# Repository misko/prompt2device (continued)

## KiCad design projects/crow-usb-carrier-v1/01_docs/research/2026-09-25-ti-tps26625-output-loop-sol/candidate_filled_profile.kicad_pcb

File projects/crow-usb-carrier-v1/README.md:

# crow-usb-carrier-v1

PCB commissioning scaffold. The original request and acceptance criteria live in [`01_docs/BRIEF.md`](01_docs/BRIEF.md); current work lives in [`01_docs/STATUS.md`](01_docs/STATUS.md).

## Capability

- target: `design`
- signal integrity: `high_speed_digital`
- assembly: `jlcpcb`
- firmware: `forbidden`
- foreign mating: `false`
- enclosure seed: `false`

The machine-readable authority is [`01_docs/capability-profile.json`](01_docs/capability-profile.json).

## Start

Run this from the project root. If this project is outside the circuits checkout, export `CIRCUITS_ROOT=/absolute/path/to/circuits` first.

```bash
export CIRCUITS_ROOT="${CIRCUITS_ROOT:-$(git rev-parse --show-toplevel 2>/dev/null)}"
test -f "$CIRCUITS_ROOT/skills/pcb-design/SKILL.md" || { \
  echo "set CIRCUITS_ROOT to the circuits checkout" >&2; exit 2; }
python3 "$CIRCUITS_ROOT/skills/pcb-design/scripts/skill_reference_router.py" \
  --profile "$PWD/01_docs/capability-profile.json" \
  --at-stage PCB-COMMISSION --json
```

This is a scaffold, not a passed commission. Read [`01_docs/COMMISSIONING-HOLD.md`](01_docs/COMMISSIONING-HOLD.md), preserve the original brief, close its fact locks, and replace or explicitly adopt every seeded example. Do not run either rebuild conductor while the hold exists; both fail closed.

Current source state is a reviewed 569-component / 65-reference ADC proposal,
including the planned `C_ADC_3V3X_OK_VDD` supervisor bypass and a project-only
P-MOD ordering repair. It has no new producer, schematic checkpoint, native
board, P2 acceptance, or release status. Earlier 568-component generated
artifacts remain historical evidence and must not be rebound; see
[`01_docs/STATUS.md`](01_docs/STATUS.md) before any conductor admission.

The current CJ is `1f01be73…` and is conditionally bound only to the reviewed
source E-FAULT clarification; complete fitted-board waveform qualification is
still required. The reviewed 18-pose power source backtrack is planned
placement, not native acceptance.

After the separately typed commission, architecture, and sourcing admission evidence is reviewed and its hold is removed, start the full conductor with `bash 03_src/rebuild_all.sh`. A fresh run deliberately stops at evidence and operator checkpoints. After accepting the exact schematic review checkpoint, continue without rebuilding TSX using `bash 03_src/rebuild_all.sh --resume-after-schematic-review`. A sealed release is immutable and does not by itself mean this board was ordered.

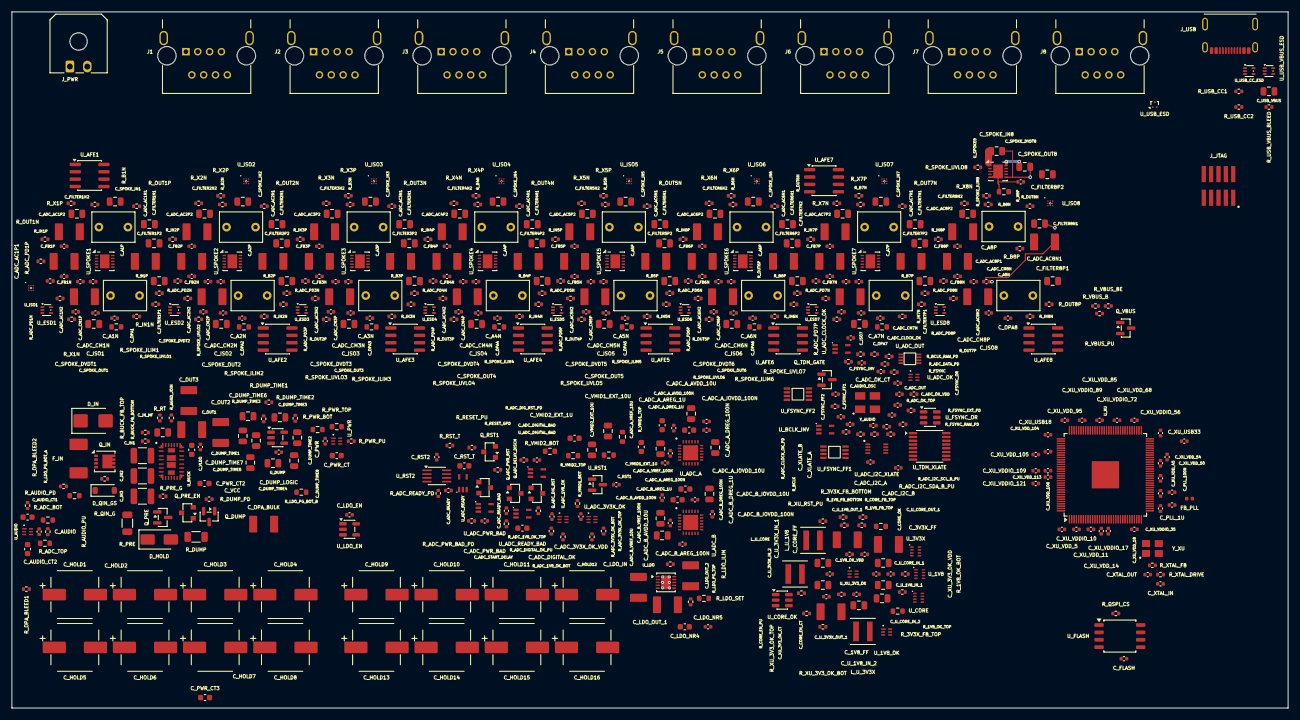
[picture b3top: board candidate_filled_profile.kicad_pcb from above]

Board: 4 copper layers, 220.0 x 120.0 mm, 569 parts (0 on the bottom side), 282 nets.

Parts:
C_1V8_FF, C_3V3X_FF: 120pF; C_0402_1005Metric
C_1V8_OK_VDD: 100nF; C_0402_1005Metric
C_A1N, C_A1P, C_A2N, C_A2P, C_A3N, C_A3P, C_A4N, C_A4P, C_A5N, C_A5P, C_A6N, C_A6P, C_A7N, C_A7P, C_A8N, C_A8P: 1uF; C_Rect_L7.2mm_W5.0mm_P5.00mm
C_ADC_3V3X_OK_VDD: 100nF; C_0402_1005Metric
C_ADC_AC1N1, C_ADC_AC1N2, C_ADC_AC1P1, C_ADC_AC1P2, C_ADC_AC2N1, C_ADC_AC2N2, C_ADC_AC2P1, C_ADC_AC2P2, C_ADC_AC3N1, C_ADC_AC3N2, C_ADC_AC3P1, C_ADC_AC3P2, C_ADC_AC4N1, C_ADC_AC4N2, C_ADC_AC4P1, C_ADC_AC4P2, C_ADC_AC5N1, C_ADC_AC5N2, C_ADC_AC5P1, C_ADC_AC5P2, C_ADC_AC6N1, C_ADC_AC6N2, C_ADC_AC6P1, C_ADC_AC6P2, C_ADC_AC7N1, C_ADC_AC7N2, C_ADC_AC7P1, C_ADC_AC7P2, C_ADC_AC8N1, C_ADC_AC8N2, C_ADC_AC8P1, C_ADC_AC8P2: 47uF; Murata_GRM32E_1210
C_ADC_A_AREG_1U: 1uF; C_0603_1608Metric
C_ADC_A_AREG_100N: 100nF; C_0402_1005Metric
C_ADC_A_AVDD_10U: 10uF; C_0805_2012Metric
C_ADC_A_AVDD_100N: 100nF; C_0402_1005Metric
C_ADC_A_DREG_1U: 1uF; C_0603_1608Metric
C_ADC_A_DREG_100N: 100nF; C_0402_1005Metric
C_ADC_A_IOVDD_10U: 10uF; C_0805_2012Metric
C_ADC_A_IOVDD_100N: 100nF; C_0402_1005Metric
C_ADC_A_VREF_10U: 10uF; C_0805_2012Metric
C_ADC_A_VREF_100N: 100nF; C_0402_1005Metric
C_ADC_B_AREG_1U: 1uF; C_0603_1608Metric
C_ADC_B_AREG_100N: 100nF; C_0402_1005Metric
C_ADC_B_AVDD_10U: 10uF; C_0805_2012Metric
C_ADC_B_AVDD_100N: 100nF; C_0402_1005Metric
C_ADC_B_DREG_1U: 1uF; C_0603_1608Metric
C_ADC_B_DREG_100N: 100nF; C_0402_1005Metric
C_ADC_B_IOVDD_10U: 10uF; C_0805_2012Metric
C_ADC_B_IOVDD_100N: 100nF; C_0402_1005Metric
C_ADC_B_VREF_10U: 10uF; C_0805_2012Metric
C_ADC_B_VREF_100N: 100nF; C_0402_1005Metric
C_ADC_CLOCK_OK: 100nF; C_0402_1005Metric
C_ADC_CM1N, C_ADC_CM1P, C_ADC_CM2N, C_ADC_CM2P, C_ADC_CM3N, C_ADC_CM3P, C_ADC_CM4N, C_ADC_CM4P, C_ADC_CM5N, C_ADC_CM5P, C_ADC_CM6N, C_ADC_CM6P, C_ADC_CM7N, C_ADC_CM7P, C_ADC_CM8N, C_ADC_CM8P: 1nF; C_0402_1005Metric
C_ADC_DIGITAL_BAD: 100nF; C_0402_1005Metric
C_ADC_DIGITAL_OK: 100nF; C_0402_1005Metric
C_ADC_I2C_A, C_ADC_I2C_B: 100nF; C_0402_1005Metric
C_ADC_OK_CT: 1nF; C_0402_1005Metric
C_ADC_OK_VDD: 100nF; C_0402_1005Metric
C_ADC_OUT: 100nF; C_0402_1005Metric
C_ADC_PWR_BAD: 100nF; C_0402_1005Metric
C_ADC_READY: 100nF; C_0402_1005Metric
C_ADC_READY_BAD: 100nF; C_0402_1005Metric
C_ADC_START_DELAY: 470nF; C_0603_1608Metric
C_AUDIO: 100nF; C_0402_1005Metric
C_AUDIO_CT1, C_AUDIO_CT2: 1uF; C_0603_1608Metric
C_AUDIO_OSC: 10nF; C_0402_1005Metric
C_CORE_EN_CT: 10nF; C_0402_1005Metric
C_CORE_FF: 120pF; C_0402_1005Metric
C_CORE_OK: 100nF; C_0402_1005Metric
C_DUMP_LOGIC: 100nF; C_0402_1005Metric
C_DUMP_TIME1, C_DUMP_TIME2, C_DUMP_TIME3, C_DUMP_TIME4, C_DUMP_TIME5, C_DUMP_TIME6, C_DUMP_TIME7, C_DUMP_TIME8: 15nF; C_0805_2012Metric
C_FB1N, C_FB1P, C_FB2N, C_FB2P, C_FB3N, C_FB3P, C_FB4N, C_FB4P, C_FB5N, C_FB5P, C_FB6N, C_FB6P, C_FB7N, C_FB7P, C_FB8N, C_FB8P: 680pF; C_0402_1005Metric
C_FILTER1N1, C_FILTER1N2, C_FILTER1P1, C_FILTER1P2, C_FILTER2N1, C_FILTER2N2, C_FILTER2P1, C_FILTER2P2, C_FILTER3N1, C_FILTER3N2, C_FILTER3P1, C_FILTER3P2, C_FILTER4N1, C_FILTER4N2, C_FILTER4P1, C_FILTER4P2, C_FILTER5N1, C_FILTER5N2, C_FILTER5P1, C_FILTER5P2, C_FILTER6N1, C_FILTER6N2, C_FILTER6P1, C_FILTER6P2, C_FILTER7N1, C_FILTER7N2, C_FILTER7P1, C_FILTER7P2, C_FILTER8N1, C_FILTER8N2, C_FILTER8P1, C_FILTER8P2: 15nF; C_0805_2012Metric
C_FLASH: 100nF; C_0402_1005Metric
C_FSYNC_FF1, C_FSYNC_FF2: 100nF; C_0402_1005Metric
C_FSYNC_INV: 100nF; C_0402_1005Metric
C_FSYNC_OR: 100nF; C_0402_1005Metric
C_HOLD1, C_HOLD2, C_HOLD3, C_HOLD4, C_HOLD5, C_HOLD6, C_HOLD7, C_HOLD8, C_HOLD9, C_HOLD10, C_HOLD11, C_HOLD12, C_HOLD13, C_HOLD14, C_HOLD15, C_HOLD16: 470uF; Panasonic_EEEFK1A471P_8x10.2_Exact
C_IN1, C_IN2, C_IN3: 10uF; C_1210_3225Metric
C_IN_HF: 100nF; C_0805_2012Metric
C_ISO1, C_ISO2, C_ISO3, C_ISO4, C_ISO5, C_ISO6, C_ISO7, C_ISO8: 100nF; C_0402_1005Metric
C_LDO_EN: 100nF; C_0402_1005Metric
C_LDO_IN: 47uF; Murata_GRM32E_1210
C_LDO_NR4: 4.7uF; C_0603_1608Metric
C_LDO_NR5: 1nF; C_0402_1005Metric
C_LDO_OUT_1, C_LDO_OUT_2: 47uF; Murata_GRM32E_1210
C_OPA1, C_OPA2, C_OPA3, C_OPA4, C_OPA5, C_OPA6, C_OPA7, C_OPA8: 100nF; C_0402_1005Metric
C_OPA_BULK: 47uF; Murata_GRM32E_1210
C_OUT1, C_OUT2, C_OUT3: 47uF; Murata_GRM32E_1210
C_PLL_1U: 1uF; C_0402_1005Metric
C_PLL_100N: 100nF; C_0402_1005Metric
C_PWR: 100nF; C_0402_1005Metric
C_PWR_CT, C_PWR_CT2, C_PWR_CT3: 1uF; C_0603_1608Metric
C_RST1, C_RST2: 100nF; C_0402_1005Metric
C_RST_T: 220nF; C_0603_1608Metric
C_SPOKE_DVDT1, C_SPOKE_DVDT2, C_SPOKE_DVDT3, C_SPOKE_DVDT4, C_SPOKE_DVDT5, C_SPOKE_DVDT6, C_SPOKE_DVDT7, C_SPOKE_DVDT8: 10nF; C_0402_1005Metric
C_SPOKE_IN1, C_SPOKE_IN2, C_SPOKE_IN3, C_SPOKE_IN4, C_SPOKE_IN5, C_SPOKE_IN6, C_SPOKE_IN7, C_SPOKE_IN8: 100nF; C_0805_2012Metric
C_SPOKE_OUT1, C_SPOKE_OUT2, C_SPOKE_OUT3, C_SPOKE_OUT4, C_SPOKE_OUT5, C_SPOKE_OUT6, C_SPOKE_OUT7, C_SPOKE_OUT8: 100nF; C_0805_2012Metric
C_USB_VBUS: 4.7uF; C_0805_2012Metric
C_U_1V8_IN_1, C_U_1V8_IN_2, C_U_3V3X_IN_1, C_U_3V3X_IN_2: 10uF; C_0805_2012Metric
C_U_1V8_OUT_1, C_U_3V3X_OUT_1: 47uF; Murata_GRM32E_1210
C_U_CORE_IN_1, C_U_CORE_IN_2: 10uF; C_0805_2012Metric
C_U_CORE_OUT_1: 47uF; Murata_GRM32E_1210
C_VCC: 1uF; C_0603_1608Metric
C_VLDO: 100nF; C_0402_1005Metric
C_VMID1_EXT_1U, C_VMID2_EXT_1U: 1uF; C_0603_1608Metric
C_VMID1_EXT_10U, C_VMID2_EXT_10U: 10uF; C_0805_2012Metric
C_XLATE_A: 100nF; C_0402_1005Metric
C_XLATE_B: 100nF; C_0402_1005Metric
C_XTAL_IN: 22pF; C_0402_1005Metric
C_XTAL_OUT: 22pF; C_0402_1005Metric
C_XU_3V3_OK_CT: 1nF; C_0402_1005Metric
C_XU_3V3_OK_VDD: 100nF; C_0402_1005Metric
C_XU_USB18, C_XU_USB33: 100nF; C_0402_1005Metric
C_XU_VDDIO_10, C_XU_VDDIO_17, C_XU_VDDIO_35, C_XU_VDDIO_56, C_XU_VDDIO_72, C_XU_VDDIO_89, C_XU_VDDIO_109, C_XU_VDDIO_121: 100nF; C_0402_1005Metric
C_XU_VDD_5, C_XU_VDD_11, C_XU_VDD_14, C_XU_VDD_18, C_XU_VDD_39, C_XU_VDD_45, C_XU_VDD_50, C_XU_VDD_54, C_XU_VDD_68, C_XU_VDD_85, C_XU_VDD_95, C_XU_VDD_104, C_XU_VDD_105, C_XU_VDD_106, C_XU_VDD_113: 100nF; C_0402_1005Metric
D_HOLD: B340A-13-F; D_SMA
D_IN: SMBJ15A; Littelfuse_SMBJ15A_SMB
D_QIN_GS: BZT52C12-13-F; D_SOD-123
FB_PLL: BLM15AG601SN1D; L_0402_1005Metric
F_IN: 0451004.MRL; Littelfuse_451_Nano2_2410
J1, J2, J3, J4, J5, J6, J7, J8: 615008160221; Wurth_615008160221_RJ45
J_JTAG: FTSH-105-01-L-DV-K; Samtec_FTSH_105_01_L_DV_K
J_PWR: 43650-0200; Molex_43650-0200
J_USB: USB4215-03-A; GCT_USB4215_03_A
L_U_1V8, L_U_3V3X: XFL4015-471MEC; Coilcraft_XFL4015_471MEC
L_U_CORE: XFL4015-471MEC; Coilcraft_XFL4015_471MEC
Q_ADC_DELAY_DISCH: 2N7002K-7; Diodes_2N7002K_SOT23_Exact
Q_ADC_DIG_RST: 2N7002K-7; Diodes_2N7002K_SOT23_Exact
Q_ADC_PWR_RST: 2N7002K-7; Diodes_2N7002K_SOT23_Exact
Q_DUMP: AO3400A; SOT-23
Q_IN: DMP6023LFG-13; Diodes_DMP6023LFG_PowerDI3333_8
Q_PRE: AO3401A; SOT-23
Q_PRE_EN: 2N7002K-7; Diodes_2N7002K_SOT23_Exact
Q_RST1: 2N7002K-7; Diodes_2N7002K_SOT23_Exact
Q_TDM_GATE: AO3400A; SOT-23
Q_VBUS: AO3400A; SOT-23
R_1V8_FB_BOTTOM, R_1V8_OK_BOT: 100kΩ; R_0402_1005Metric
R_1V8_FB_TOP: 210kΩ; R_0402_1005Metric
R_1V8_OK_TOP: 52.3kΩ; R_0402_1005Metric
R_3V3X_FB_BOTTOM: 100kΩ; R_0603_1608Metric
R_3V3X_FB_TOP: 453kΩ; R_0603_1608Metric
R_ADC_1V8_OK_BOT, R_ADC_3V3X_OK_BOT: 100kΩ; R_0402_1005Metric
R_ADC_1V8_OK_TOP: 52.3kΩ; R_0402_1005Metric
R_ADC_3V3X_OK_TOP: 169kΩ; R_0402_1005Metric
R_ADC_BOT: 10kΩ; R_0603_1608Metric
R_ADC_CLOCK_OK_PD: 100kΩ; R_0402_1005Metric
R_ADC_DATA_PD: 100kΩ; R_0402_1005Metric
R_ADC_DELAY_GATE_PD: 100kΩ; R_0402_1005Metric
R_ADC_DIGITAL_OK_PU: 10kΩ; R_0402_1005Metric
R_ADC_DIG_RST_PD: 100kΩ; R_0402_1005Metric
R_ADC_I2C_SCL_A_PU, R_ADC_I2C_SCL_B_PU, R_ADC_I2C_SDA_A_PU, R_ADC_I2C_SDA_B_PU: 4.7kΩ; R_0402_1005Metric
R_ADC_OK_BOT: 100kΩ; R_0402_1005Metric
R_ADC_OK_PU: 10kΩ; R_0402_1005Metric
R_ADC_OK_TOP: 169kΩ; R_0402_1005Metric
R_ADC_PD1N, R_ADC_PD1P, R_ADC_PD2N, R_ADC_PD2P, R_ADC_PD3N, R_ADC_PD3P, R_ADC_PD4N, R_ADC_PD4P, R_ADC_PD5N, R_ADC_PD5P, R_ADC_PD6N, R_ADC_PD6P, R_ADC_PD7N, R_ADC_PD7P, R_ADC_PD8N, R_ADC_PD8P: 10kΩ; R_0402_1005Metric
R_ADC_PWR_BAD_PD: 100kΩ; R_0402_1005Metric
R_ADC_READY_PD: 100kΩ; R_0402_1005Metric
R_ADC_START_DELAY: 100kΩ; R_0402_1005Metric
R_ADC_TOP: 17.4kΩ; R_0603_1608Metric
R_AGND_JOIN: 0Ω; R_0402_1005Metric
R_AUDIO_PD: 100kΩ; R_0402_1005Metric
R_AUDIO_PU: 10kΩ; R_0402_1005Metric
R_B1N, R_B1P, R_B2N, R_B2P, R_B3N, R_B3P, R_B4N, R_B4P, R_B5N, R_B5P, R_B6N, R_B6P, R_B7N, R_B7P, R_B8N, R_B8P: 100kΩ; R_0402_1005Metric
R_BCLK: 33Ω; R_0402_1005Metric
R_BCLK_RAW_PD: 100kΩ; R_0402_1005Metric
R_BUCK_FB_BOTTOM: 10kΩ; R_0402_1005Metric
R_BUCK_FB_TOP: 40.2kΩ; R_0402_1005Metric
R_CORE_EN_PU: 10kΩ; R_0402_1005Metric
R_CORE_FB_BOTTOM: 100kΩ; R_0402_1005Metric
R_CORE_FB_TOP: 49.9kΩ; R_0402_1005Metric
R_DUMP: 1Ω; R_1206_3216Metric
R_DUMP_PD: 100kΩ; R_0402_1005Metric
R_DUMP_TIME1, R_DUMP_TIME2, R_DUMP_TIME3: 100kΩ; R_0402_1005Metric
R_FSYNC: 33Ω; R_0402_1005Metric
R_FSYNC_EXT_PD: 100kΩ; R_0402_1005Metric
R_FSYNC_RAW_PD: 100kΩ; R_0402_1005Metric
R_IN1N, R_IN1P, R_IN2N, R_IN2P, R_IN3N, R_IN3P, R_IN4N, R_IN4P, R_IN5N, R_IN5P, R_IN6N, R_IN6P, R_IN7N, R_IN7P, R_IN8N, R_IN8P: 10kΩ; R_0402_1005Metric
R_LDO_ILIM: 300Ω; R_0402_1005Metric
R_LDO_PG_BOT_A: 10kΩ; R_0603_1608Metric
R_LDO_PG_BOT_B: 1kΩ; R_0603_1608Metric
R_LDO_PG_TOP: 100kΩ; R_0402_1005Metric
R_LDO_SET: 33kΩ; R_0603_1608Metric
R_OPA_BLEED1, R_OPA_BLEED2: 100Ω; R_0402_1005Metric
R_OUT1N, R_OUT1P, R_OUT2N, R_OUT2P, R_OUT3N, R_OUT3P, R_OUT4N, R_OUT4P, R_OUT5N, R_OUT5P, R_OUT6N, R_OUT6P, R_OUT7N, R_OUT7P, R_OUT8N, R_OUT8P: 10Ω; R_0402_1005Metric
R_PRE: 22Ω; R_1206_3216Metric
R_PRE_G: 100kΩ; R_0402_1005Metric
R_PWR_BOT: 10kΩ; R_0603_1608Metric
R_PWR_PU: 10kΩ; R_0402_1005Metric
R_PWR_TOP: 30.9kΩ; Yageo_RT0603_NominalBody
R_QIN_G: 100kΩ; R_0402_1005Metric
R_QSPI_CS: 4.7kΩ; R_0402_1005Metric
R_RESET_GPD: 100kΩ; R_0402_1005Metric
R_RESET_PU: 10kΩ; R_0402_1005Metric
R_RST_T: 100kΩ; R_0402_1005Metric
R_RT: 13kΩ; R_0402_1005Metric
R_SPOKE_ILIM1, R_SPOKE_ILIM2, R_SPOKE_ILIM3, R_SPOKE_ILIM4, R_SPOKE_ILIM5, R_SPOKE_ILIM6, R_SPOKE_ILIM7, R_SPOKE_ILIM8: 44.2kΩ; Yageo_RT0603_NominalBody
R_SPOKE_UVLO1, R_SPOKE_UVLO2, R_SPOKE_UVLO3, R_SPOKE_UVLO4, R_SPOKE_UVLO5, R_SPOKE_UVLO6, R_SPOKE_UVLO7, R_SPOKE_UVLO8: 1MΩ; R_0402_1005Metric
R_TDM_OE_PU: 10kΩ; R_0402_1005Metric
R_USB_CC1, R_USB_CC2: 5.1kΩ; R_0402_1005Metric
R_USB_VBUS_BLEED: 47kΩ; R_0402_1005Metric
R_VBUS_B: 100kΩ; R_0402_1005Metric
R_VBUS_BE: 1MΩ; R_0402_1005Metric
R_VBUS_PU: 10kΩ; R_0402_1005Metric
R_VMID1_BOT, R_VMID1_TOP, R_VMID2_BOT, R_VMID2_TOP: 1kΩ; R_0603_1608Metric
R_X1N, R_X1P, R_X2N, R_X2P, R_X3N, R_X3P, R_X4N, R_X4P, R_X5N, R_X5P, R_X6N, R_X6P, R_X7N, R_X7P, R_X8N, R_X8P: 300Ω; R_0402_1005Metric
R_XTAL_DRIVE: 680Ω; R_0402_1005Metric
R_XTAL_FB: 1MΩ; R_0402_1005Metric
R_XU_3V3_OK_BOT: 100kΩ; R_0402_1005Metric
R_XU_3V3_OK_TOP: 169kΩ; R_0402_1005Metric
R_XU_RST_PU: 10kΩ; R_0402_1005Metric
U_1V8, U_3V3X: TPS62822DLCR; TI_DLC0008B_VSON_HR8
U_1V8_OK: TPS389001DSER; TI_DSE0006A_Exact
U_ADC_1V8_OK, U_ADC_3V3X_OK: TPS389001DSER; TI_DSE0006A_Exact
U_ADC_A: TLV320ADC6140IRTWT; TI_RTW0024A_WQFN24_4x4_EP2.6
U_ADC_B: TLV320ADC6140IRTWT; TI_RTW0024A_WQFN24_4x4_EP2.6
U_ADC_CLOCK_OK: SN74LVC1G125DCKT; TI_DCK0005A_SC70_5
U_ADC_DIGITAL_BAD: SN74LVC1G04DCKR; TI_DCK0005A_SC70_5
U_ADC_I2C_XLATE: TCA9406DCUR; TI_TCA9406_DCU0008A_VSSOP8
U_ADC_OK: TPS389001DSER; TI_DSE0006A_Exact
U_ADC_OUT: SN74AUP3G34DCUR; TI_DCU0008A_VSSOP8
U_ADC_PWR_BAD: SN74LVC1G04DCKR; TI_DCK0005A_SC70_5
U_ADC_READY: SN74LVC1G125DCKT; TI_DCK0005A_SC70_5
U_ADC_READY_BAD: SN74LVC1G04DCKR; TI_DCK0005A_SC70_5
U_AFE1, U_AFE2, U_AFE3, U_AFE4, U_AFE5, U_AFE6, U_AFE7, U_AFE8: OPA2320AIDR; SOIC-8_3.9x4.9mm_P1.27mm
U_AUDIO: TPS389001DSER; TI_DSE0006A_Exact
U_BCLK_INV: SN74LVC1G04DCKR; TI_DCK0005A_SC70_5
U_BUCK: TPSM63603RDHR; TPSM63603RDHR_RDH0030A
U_CORE: TPS62822DLCR; TI_DLC0008B_VSON_HR8
U_CORE_OK: TPS3808G09DBVR; SOT-23-6
U_DUMP: 74LVC1G14GV,125; SOT-23-5
U_ESD1, U_ESD2, U_ESD3, U_ESD4, U_ESD5, U_ESD6, U_ESD7, U_ESD8: TPD2E2U06DRLR; TI_DRL0005A_TPD2E2U06
U_FLASH: W25Q128JWSIQ; SOIC-8_5.3x5.3mm_P1.27mm
U_FSYNC_FF1, U_FSYNC_FF2: SN74LVC2G74DCTR; TI_DCT0008A_SM8
U_FSYNC_OR: SN74LVC1G332DBVR; SOT-23-6
U_ISO1, U_ISO2, U_ISO3, U_ISO4, U_ISO5, U_ISO6, U_ISO7, U_ISO8: TMUX4827YBHR; TI_YBH0009_C02_TMUX4827
U_LDO: LT3045EDD#PBF; ADI_LT3045_DD_NoHoles
U_LDO_EN: 74LVC1G14GV,125; SOT-23-5
U_PWR: TPS389001DSER; TI_DSE0006A_Exact
U_RST1: TPS3839K33DBZR; SOT-23
U_RST2: SN74LVC1G123DCTR; SSOP-8_2.95x2.8mm_P0.65mm
U_SPOKE1, U_SPOKE2, U_SPOKE3, U_SPOKE4, U_SPOKE5, U_SPOKE6, U_SPOKE7, U_SPOKE8: TPS26625DRCR; TI_DRC0010J_VSON10
U_TDM_XLATE: SN74AXC4T245PWR; TSSOP-16_4.4x5mm_P0.65mm
U_USB_CC_ESD: TPD2E2U06DRLR; TI_DRL0005A_TPD2E2U06
U_USB_ESD: TPD2EUSB30ADRTR; Texas_DRT-3
U_USB_VBUS_ESD: TPD2E2U06DRLR; TI_DRL0005A_TPD2E2U06
U_XU: XU316-1024-TQ128-C24; TQFP-128_14x14mm_P0.4mm_EP_XU316
U_XU_3V3_OK: TPS389001DSER; TI_DSE0006A_Exact
Y_AUDIO: SX5M24.576M20F30TNN; SCTF_SX5M_5032
Y_XU: X322524MOB4SI; YXC_YSX321SL_3225_4Pin

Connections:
ADC1N: C_ADC_AC1N1.2, C_ADC_AC1N2.2, C_ADC_CM1N.1, U_ADC_A.13
ADC1P: C_ADC_AC1P1.2, C_ADC_AC1P2.2, C_ADC_CM1P.1, U_ADC_A.12
ADC2N: C_ADC_AC2N1.2, C_ADC_AC2N2.2, C_ADC_CM2N.1, U_ADC_A.11
ADC2P: C_ADC_AC2P1.2, C_ADC_AC2P2.2, C_ADC_CM2P.1, U_ADC_A.10
ADC3N: C_ADC_AC3N1.2, C_ADC_AC3N2.2, C_ADC_CM3N.1, U_ADC_A.9
ADC3P: C_ADC_AC3P1.2, C_ADC_AC3P2.2, C_ADC_CM3P.1, U_ADC_A.8
ADC4N: C_ADC_AC4N1.2, C_ADC_AC4N2.2, C_ADC_CM4N.1, U_ADC_A.7
ADC4P: C_ADC_AC4P1.2, C_ADC_AC4P2.2, C_ADC_CM4P.1, U_ADC_A.6
ADC5N: C_ADC_AC5N1.2, C_ADC_AC5N2.2, C_ADC_CM5N.1, U_ADC_B.7
ADC5P: C_ADC_AC5P1.2, C_ADC_AC5P2.2, C_ADC_CM5P.1, U_ADC_B.6
ADC6N: C_ADC_AC6N1.2, C_ADC_AC6N2.2, C_ADC_CM6N.1, U_ADC_B.9
ADC6P: C_ADC_AC6P1.2, C_ADC_AC6P2.2, C_ADC_CM6P.1, U_ADC_B.8
ADC7N: C_ADC_AC7N1.2, C_ADC_AC7N2.2, C_ADC_CM7N.1, U_ADC_B.11
ADC7P: C_ADC_AC7P1.2, C_ADC_AC7P2.2, C_ADC_CM7P.1, U_ADC_B.10
ADC8N: C_ADC_AC8N1.2, C_ADC_AC8N2.2, C_ADC_CM8N.1, U_ADC_B.13
ADC8P: C_ADC_AC8P1.2, C_ADC_AC8P2.2, C_ADC_CM8P.1, U_ADC_B.12
ADC_A_AREG: C_ADC_A_AREG_1U.1, C_ADC_A_AREG_100N.1, U_ADC_A.2
ADC_A_DREG: C_ADC_A_DREG_1U.1, C_ADC_A_DREG_100N.1, U_ADC_A.24
ADC_A_VREF: C_ADC_A_VREF_10U.1, C_ADC_A_VREF_100N.1, U_ADC_A.3
ADC_BCLK: R_BCLK.2, U_ADC_A.22, U_ADC_B.22
ADC_BCLK_INV: U_BCLK_INV.4, U_FSYNC_FF2.1
ADC_BCLK_RAW: R_BCLK_RAW_PD.1, U_ADC_OUT.3, U_BCLK_INV.2, U_FSYNC_FF1.1, U_TDM_XLATE.13
ADC_BCLK_SAFE: R_BCLK.1, U_ADC_OUT.5
ADC_B_AREG: C_ADC_B_AREG_1U.1, C_ADC_B_AREG_100N.1, U_ADC_B.2
ADC_B_DREG: C_ADC_B_DREG_1U.1, C_ADC_B_DREG_100N.1, U_ADC_B.24
ADC_B_VREF: C_ADC_B_VREF_10U.1, C_ADC_B_VREF_100N.1, U_ADC_B.3
ADC_CLOCK_OK: Q_TDM_GATE.1, R_ADC_CLOCK_OK_PD.1, U_ADC_CLOCK_OK.4
ADC_DIGITAL_BAD: Q_ADC_DIG_RST.1, R_ADC_DIG_RST_PD.1, U_ADC_CLOCK_OK.1, U_ADC_DIGITAL_BAD.4, U_ADC_READY.1
ADC_DIGITAL_OK: R_ADC_DIGITAL_OK_PU.2, U_ADC_1V8_OK.6, U_ADC_3V3X_OK.6, U_ADC_DIGITAL_BAD.2
ADC_DOUT1: R_ADC_DATA_PD.1, U_ADC_A.21, U_ADC_B.21, U_TDM_XLATE.10
ADC_DUMP: Q_DUMP.3, R_DUMP.2
ADC_FSYNC: R_FSYNC.2, U_ADC_A.23, U_ADC_B.23
ADC_FSYNC_EXT: R_FSYNC_EXT_PD.1, U_ADC_OUT.6, U_FSYNC_OR.4
ADC_FSYNC_RAW: R_FSYNC_RAW_PD.1, U_FSYNC_FF1.2, U_FSYNC_OR.1, U_TDM_XLATE.12
ADC_FSYNC_SAFE: R_FSYNC.1, U_ADC_OUT.2
ADC_I2C_SCL: R_ADC_I2C_SCL_B_PU.1, U_ADC_A.17, U_ADC_B.17, U_ADC_I2C_XLATE.8
ADC_I2C_SDA: R_ADC_I2C_SDA_B_PU.1, U_ADC_A.18, U_ADC_B.18, U_ADC_I2C_XLATE.1
ADC_OK: R_ADC_OK_PU.2, U_ADC_CLOCK_OK.2, U_ADC_OK.6, U_FSYNC_FF1.6, U_FSYNC_FF2.6
ADC_OK_CT: C_ADC_OK_CT.1, U_ADC_OK.5
ADC_PWR_BAD: Q_ADC_PWR_RST.1, R_ADC_PWR_BAD_PD.1, U_ADC_PWR_BAD.4
ADC_READY: R_ADC_READY_PD.1, R_ADC_START_DELAY.1, U_ADC_I2C_XLATE.6, U_ADC_READY.4, U_ADC_READY_BAD.2, U_RST2.3
ADC_READY_BAD: Q_ADC_DELAY_DISCH.1, R_ADC_DELAY_GATE_PD.1, U_ADC_READY_BAD.4
ADC_RESET_N: Q_ADC_DIG_RST.3, Q_ADC_PWR_RST.3, Q_RST1.3, R_RESET_PU.2, U_ADC_A.14, U_ADC_B.14
ADC_SENSE: R_ADC_BOT.1, R_ADC_TOP.2, U_AUDIO.1
ADC_START_DELAY: C_ADC_START_DELAY.1, Q_ADC_DELAY_DISCH.3, R_ADC_START_DELAY.2, U_RST2.2
AIN_N1: R_IN1N.2, U_AFE1.5
AIN_N2: R_IN2N.2, U_AFE2.5
AIN_N3: R_IN3N.2, U_AFE3.5
AIN_N4: R_IN4N.2, U_AFE4.5
AIN_N5: R_IN5N.2, U_AFE5.5
AIN_N6: R_IN6N.2, U_AFE6.5
AIN_N7: R_IN7N.2, U_AFE7.5
AIN_N8: R_IN8N.2, U_AFE8.5
AIN_P1: R_IN1P.2, U_AFE1.3
AIN_P2: R_IN2P.2, U_AFE2.3
AIN_P3: R_IN3P.2, U_AFE3.3
AIN_P4: R_IN4P.2, U_AFE4.3
AIN_P5: R_IN5P.2, U_AFE5.3
AIN_P6: R_IN6P.2, U_AFE6.3
AIN_P7: R_IN7P.2, U_AFE7.3
AIN_P8: R_IN8P.2, U_AFE8.3
AUDIO_24M576: U_TDM_XLATE.11, Y_AUDIO.3
AUDIO_CT: C_AUDIO_CT1.1, C_AUDIO_CT2.1, U_AUDIO.5
AUDIO_EN: R_AUDIO_PD.1, R_AUDIO_PU.2, U_AUDIO.6, U_ISO1.2, U_ISO2.2, U_ISO3.2, U_ISO4.2, U_ISO5.2, U_ISO6.2, U_ISO7.2, U_ISO8.2
AUDIO_MCLK_1V8: U_TDM_XLATE.6, U_XU.23
AUDIO_N1: C_A1N.1, J1.4, U_ESD1.5
AUDIO_N2: C_A2N.1, J2.4, U_ESD2.5
AUDIO_N3: C_A3N.1, J3.4, U_ESD3.5
AUDIO_N4: C_A4N.1, J4.4, U_ESD4.5
AUDIO_N5: C_A5N.1, J5.4, U_ESD5.5
AUDIO_N6: C_A6N.1, J6.4, U_ESD6.5
AUDIO_N7: C_A7N.1, J7.4, U_ESD7.5
AUDIO_N8: C_A8N.1, J8.4, U_ESD8.5
AUDIO_P1: C_A1P.1, J1.5, U_ESD1.3
AUDIO_P2: C_A2P.1, J2.5, U_ESD2.3
AUDIO_P3: C_A3P.1, J3.5, U_ESD3.3
AUDIO_P4: C_A4P.1, J4.5, U_ESD4.3
AUDIO_P5: C_A5P.1, J5.5, U_ESD5.3
AUDIO_P6: C_A6P.1, J6.5, U_ESD6.3
AUDIO_P7: C_A7P.1, J7.5, U_ESD7.3
AUDIO_P8: C_A8P.1, J8.5, U_ESD8.3
BIAS_N1: C_A1N.2, R_B1N.1, R_IN1N.1
BIAS_N2: C_A2N.2, R_B2N.1, R_IN2N.1
BIAS_N3: C_A3N.2, R_B3N.1, R_IN3N.1
BIAS_N4: C_A4N.2, R_B4N.1, R_IN4N.1
BIAS_N5: C_A5N.2, R_B5N.1, R_IN5N.1
BIAS_N6: C_A6N.2, R_B6N.1, R_IN6N.1
BIAS_N7: C_A7N.2, R_B7N.1, R_IN7N.1
BIAS_N8: C_A8N.2, R_B8N.1, R_IN8N.1
BIAS_P1: C_A1P.2, R_B1P.1, R_IN1P.1
BIAS_P2: C_A2P.2, R_B2P.1, R_IN2P.1
BIAS_P3: C_A3P.2, R_B3P.1, R_IN3P.1
BIAS_P4: C_A4P.2, R_B4P.1, R_IN4P.1
BIAS_P5: C_A5P.2, R_B5P.1, R_IN5P.1
BIAS_P6: C_A6P.2, R_B6P.1, R_IN6P.1
BIAS_P7: C_A7P.2, R_B7P.1, R_IN7P.1
BIAS_P8: C_A8P.2, R_B8P.1, R_IN8P.1
BOOT_SHORT: U_BUCK.20, U_BUCK.21
BUCK_AGND: R_AGND_JOIN.1, R_BUCK_FB_BOTTOM.2, R_RT.2, U_BUCK.24, U_BUCK.27
BUCK_FB: R_BUCK_FB_BOTTOM.1, R_BUCK_FB_TOP.2, U_BUCK.25
BUCK_RT: R_RT.1, U_BUCK.1
BUCK_VCC: C_VCC.1, U_BUCK.23
CHASSIS: J1.9, J1.10, J2.9, J2.10, J3.9, J3.10, J4.9, J4.10, J5.9, J5.10, J6.9, J6.10, J7.9, J7.10, J8.9, J8.10
CORE_EN: R_CORE_EN_PU.2, U_1V8_OK.6, U_CORE.1
CORE_EN_CT: C_CORE_EN_CT.1, U_1V8_OK.5
DUMP_GATE: Q_DUMP.1, R_DUMP_PD.1, U_DUMP.4, U_LDO_EN.2
DUMP_RC: C_DUMP_TIME1.1, C_DUMP_TIME2.1, C_DUMP_TIME3.1, C_DUMP_TIME4.1, C_DUMP_TIME5.1, C_DUMP_TIME6.1, C_DUMP_TIME7.1, C_DUMP_TIME8.1, R_DUMP_TIME2.2, R_DUMP_TIME3.2, U_DUMP.2
DUMP_RMID: R_DUMP_TIME1.2, R_DUMP_TIME2.1, R_DUMP_TIME3.1
FB_N1: C_FB1N.1, R_X1N.1, U_AFE1.6
FB_N2: C_FB2N.1, R_X2N.1, U_AFE2.6
FB_N3: C_FB3N.1, R_X3N.1, U_AFE3.6
FB_N4: C_FB4N.1, R_X4N.1, U_AFE4.6
FB_N5: C_FB5N.1, R_X5N.1, U_AFE5.6
FB_N6: C_FB6N.1, R_X6N.1, U_AFE6.6
FB_N7: C_FB7N.1, R_X7N.1, U_AFE7.6
FB_N8: C_FB8N.1, R_X8N.1, U_AFE8.6
FB_P1: C_FB1P.1, R_X1P.1, U_AFE1.2
FB_P2: C_FB2P.1, R_X2P.1, U_AFE2.2
FB_P3: C_FB3P.1, R_X3P.1, U_AFE3.2
FB_P4: C_FB4P.1, R_X4P.1, U_AFE4.2
FB_P5: C_FB5P.1, R_X5P.1, U_AFE5.2
FB_P6: C_FB6P.1, R_X6P.1, U_AFE6.2
FB_P7: C_FB7P.1, R_X7P.1, U_AFE7.2
FB_P8: C_FB8P.1, R_X8P.1, U_AFE8.2
FILTER1N: C_FILTER1N1.1, C_FILTER1N2.1, R_OUT1N.2, R_X1N.2, U_ISO1.9
FILTER1P: C_FILTER1P1.1, C_FILTER1P2.1, R_OUT1P.2, R_X1P.2, U_ISO1.7
FILTER2N: C_FILTER2N1.1, C_FILTER2N2.1, R_OUT2N.2, R_X2N.2, U_ISO2.9
FILTER2P: C_FILTER2P1.1, C_FILTER2P2.1, R_OUT2P.2, R_X2P.2, U_ISO2.7
FILTER3N: C_FILTER3N1.1, C_FILTER3N2.1, R_OUT3N.2, R_X3N.2, U_ISO3.9
FILTER3P: C_FILTER3P1.1, C_FILTER3P2.1, R_OUT3P.2, R_X3P.2, U_ISO3.7
FILTER4N: C_FILTER4N1.1, C_FILTER4N2.1, R_OUT4N.2, R_X4N.2, U_ISO4.9
FILTER4P: C_FILTER4P1.1, C_FILTER4P2.1, R_OUT4P.2, R_X4P.2, U_ISO4.7
FILTER5N: C_FILTER5N1.1, C_FILTER5N2.1, R_OUT5N.2, R_X5N.2, U_ISO5.9
FILTER5P: C_FILTER5P1.1, C_FILTER5P2.1, R_OUT5P.2, R_X5P.2, U_ISO5.7
FILTER6N: C_FILTER6N1.1, C_FILTER6N2.1, R_OUT6N.2, R_X6N.2, U_ISO6.9
FILTER6P: C_FILTER6P1.1, C_FILTER6P2.1, R_OUT6P.2, R_X6P.2, U_ISO6.7
FILTER7N: C_FILTER7N1.1, C_FILTER7N2.1, R_OUT7N.2, R_X7N.2, U_ISO7.9
FILTER7P: C_FILTER7P1.1, C_FILTER7P2.1, R_OUT7P.2, R_X7P.2, U_ISO7.7
FILTER8N: C_FILTER8N1.1, C_FILTER8N2.1, R_OUT8N.2, R_X8N.2, U_ISO8.9
FILTER8P: C_FILTER8P1.1, C_FILTER8P2.1, R_OUT8P.2, R_X8P.2, U_ISO8.7
FSYNC_Q1: U_FSYNC_FF1.5, U_FSYNC_FF2.2, U_FSYNC_OR.3
FSYNC_Q2: U_FSYNC_FF2.5, U_FSYNC_OR.6
GND: C_1V8_OK_VDD.2, C_ADC_3V3X_OK_VDD.2, C_ADC_A_AREG_1U.2, C_ADC_A_AREG_100N.2, C_ADC_A_AVDD_10U.2, C_ADC_A_AVDD_100N.2, C_ADC_A_DREG_1U.2, C_ADC_A_DREG_100N.2, C_ADC_A_IOVDD_10U.2, C_ADC_A_IOVDD_100N.2, C_ADC_A_VREF_10U.2, C_ADC_A_VREF_100N.2, C_ADC_B_AREG_1U.2, C_ADC_B_AREG_100N.2, C_ADC_B_AVDD_10U.2, C_ADC_B_AVDD_100N.2, C_ADC_B_DREG_1U.2, C_ADC_B_DREG_100N.2, C_ADC_B_IOVDD_10U.2, C_ADC_B_IOVDD_100N.2, C_ADC_B_VREF_10U.2, C_ADC_B_VREF_100N.2, C_ADC_CLOCK_OK.2, C_ADC_CM1N.2, C_ADC_CM1P.2, C_ADC_CM2N.2, C_ADC_CM2P.2, C_ADC_CM3N.2, C_ADC_CM3P.2, C_ADC_CM4N.2, C_ADC_CM4P.2, C_ADC_CM5N.2, C_ADC_CM5P.2, C_ADC_CM6N.2, C_ADC_CM6P.2, C_ADC_CM7N.2, C_ADC_CM7P.2, C_ADC_CM8N.2, C_ADC_CM8P.2, C_ADC_DIGITAL_BAD.2, C_ADC_DIGITAL_OK.2, C_ADC_I2C_A.2, C_ADC_I2C_B.2, C_ADC_OK_CT.2, C_ADC_OK_VDD.2, C_ADC_OUT.2, C_ADC_PWR_BAD.2, C_ADC_READY.2, C_ADC_READY_BAD.2, C_ADC_START_DELAY.2, C_AUDIO.2, C_AUDIO_CT1.2, C_AUDIO_CT2.2, C_AUDIO_OSC.2, C_CORE_EN_CT.2, C_CORE_OK.2, C_DUMP_LOGIC.2, C_DUMP_TIME1.2, C_DUMP_TIME2.2, C_DUMP_TIME3.2, C_DUMP_TIME4.2, C_DUMP_TIME5.2, C_DUMP_TIME6.2, C_DUMP_TIME7.2, C_DUMP_TIME8.2, C_FILTER1N1.2, C_FILTER1N2.2, C_FILTER1P1.2, C_FILTER1P2.2, C_FILTER2N1.2, C_FILTER2N2.2, C_FILTER2P1.2, C_FILTER2P2.2, C_FILTER3N1.2, C_FILTER3N2.2, C_FILTER3P1.2, C_FILTER3P2.2, C_FILTER4N1.2, C_FILTER4N2.2, C_FILTER4P1.2, C_FILTER4P2.2, C_FILTER5N1.2, C_FILTER5N2.2, C_FILTER5P1.2, C_FILTER5P2.2, C_FILTER6N1.2, C_FILTER6N2.2, C_FILTER6P1.2, C_FILTER6P2.2, C_FILTER7N1.2, C_FILTER7N2.2, C_FILTER7P1.2, C_FILTER7P2.2, C_FILTER8N1.2, C_FILTER8N2.2, C_FILTER8P1.2, C_FILTER8P2.2, C_FLASH.2, C_FSYNC_FF1.2, C_FSYNC_FF2.2, C_FSYNC_INV.2, C_FSYNC_OR.2, C_HOLD1.2, C_HOLD2.2, C_HOLD3.2, C_HOLD4.2, C_HOLD5.2, C_HOLD6.2, C_HOLD7.2, C_HOLD8.2, C_HOLD9.2, C_HOLD10.2, C_HOLD11.2, C_HOLD12.2, C_HOLD13.2, C_HOLD14.2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
ISO1N: C_ADC_AC1N1.1, C_ADC_AC1N2.1, R_ADC_PD1N.1, U_ISO1.6
ISO1P: C_ADC_AC1P1.1, C_ADC_AC1P2.1, R_ADC_PD1P.1, U_ISO1.4
ISO2N: C_ADC_AC2N1.1, C_ADC_AC2N2.1, R_ADC_PD2N.1, U_ISO2.6
ISO2P: C_ADC_AC2P1.1, C_ADC_AC2P2.1, R_ADC_PD2P.1, U_ISO2.4
ISO3N: C_ADC_AC3N1.1, C_ADC_AC3N2.1, R_ADC_PD3N.1, U_ISO3.6
ISO3P: C_ADC_AC3P1.1, C_ADC_AC3P2.1, R_ADC_PD3P.1, U_ISO3.4
ISO4N: C_ADC_AC4N1.1, C_ADC_AC4N2.1, R_ADC_PD4N.1, U_ISO4.6
ISO4P: C_ADC_AC4P1.1, C_ADC_AC4P2.1, R_ADC_PD4P.1, U_ISO4.4
ISO5N: C_ADC_AC5N1.1, C_ADC_AC5N2.1, R_ADC_PD5N.1, U_ISO5.6
ISO5P: C_ADC_AC5P1.1, C_ADC_AC5P2.1, R_ADC_PD5P.1, U_ISO5.4
ISO6N: C_ADC_AC6N1.1, C_ADC_AC6N2.1, R_ADC_PD6N.1, U_ISO6.6
ISO6P: C_ADC_AC6P1.1, C_ADC_AC6P2.1, R_ADC_PD6P.1, U_ISO6.4
ISO7N: C_ADC_AC7N1.1, C_ADC_AC7N2.1, R_ADC_PD7N.1, U_ISO7.6
ISO7P: C_ADC_AC7P1.1, C_ADC_AC7P2.1, R_ADC_PD7P.1, U_ISO7.4
ISO8N: C_ADC_AC8N1.1, C_ADC_AC8N2.1, R_ADC_PD8N.1, U_ISO8.6
ISO8P: C_ADC_AC8P1.1, C_ADC_AC8P2.1, R_ADC_PD8P.1, U_ISO8.4
JTAG_TCK: J_JTAG.4, U_XU.51
JTAG_TDI: J_JTAG.8, U_XU.36
JTAG_TDO: J_JTAG.6, U_XU.37
JTAG_TMS: J_JTAG.2, U_XU.44
LDO_EN: U_LDO.3, U_LDO_EN.4
LDO_ILIM: R_LDO_ILIM.1, U_LDO.5
LDO_NR: C_LDO_NR4.1, C_LDO_NR5.1, R_LDO_SET.1, U_LDO.7
LDO_PGFB: R_LDO_PG_BOT_A.1, R_LDO_PG_TOP.2, U_LDO.6
LDO_PGFB_BOT: R_LDO_PG_BOT_A.2, R_LDO_PG_BOT_B.1
N0V9: C_CORE_FF.1, C_U_CORE_OUT_1.1, C_XU_VDD_5.1, C_XU_VDD_11.1, C_XU_VDD_14.1, C_XU_VDD_18.1, C_XU_VDD_39.1, C_XU_VDD_45.1, C_XU_VDD_50.1, C_XU_VDD_54.1, C_XU_VDD_68.1, C_XU_VDD_85.1, C_XU_VDD_95.1, C_XU_VDD_104.1, C_XU_VDD_105.1, C_XU_VDD_106.1, C_XU_VDD_113.1, FB_PLL.1, L_U_CORE.2, R_CORE_FB_TOP.1, U_CORE_OK.5, U_XU.5, U_XU.11, U_XU.14, U_XU.18, U_XU.39, U_XU.45, U_XU.50, U_XU.54, U_XU.68, U_XU.85, U_XU.95, U_XU.104, U_XU.105, U_XU.106, U_XU.113
N1V8: C_1V8_FF.1, C_ADC_I2C_A.1, C_CORE_OK.1, C_FLASH.1, C_U_1V8_OUT_1.1, C_XLATE_A.1, C_XU_USB18.1, C_XU_VDDIO_10.1, C_XU_VDDIO_17.1, C_XU_VDDIO_35.1, C_XU_VDDIO_56.1, C_XU_VDDIO_72.1, C_XU_VDDIO_89.1, C_XU_VDDIO_109.1, C_XU_VDDIO_121.1, J_JTAG.1, L_U_1V8.2, R_1V8_FB_TOP.1, R_1V8_OK_TOP.1, R_ADC_1V8_OK_TOP.1, R_ADC_I2C_SCL_A_PU.2, R_ADC_I2C_SDA_A_PU.2, R_CORE_EN_PU.1, R_QSPI_CS.1, R_TDM_OE_PU.1, R_VBUS_PU.1, R_XU_RST_PU.1, U_ADC_I2C_XLATE.3, U_CORE_OK.3, U_CORE_OK.6, U_FLASH.8, U_TDM_XLATE.1, U_TDM_XLATE.2, U_XU.10, U_XU.17, U_XU.35, U_XU.56, U_XU.62, U_XU.72, U_XU.89, U_XU.109, U_XU.121
N3V3X: C_3V3X_FF.1, C_ADC_OK_VDD.1, C_AUDIO_OSC.1, C_FSYNC_FF1.1, C_FSYNC_FF2.1, C_FSYNC_INV.1, C_FSYNC_OR.1, C_U_3V3X_OUT_1.1, C_XLATE_B.1, C_XU_USB33.1, L_U_3V3X.2, R_3V3X_FB_TOP.1, R_ADC_3V3X_OK_TOP.1, R_ADC_OK_PU.1, R_XU_3V3_OK_TOP.1, U_ADC_OK.3, U_ADC_OK.4, U_BCLK_INV.5, U_FSYNC_FF1.7, U_FSYNC_FF1.8, U_FSYNC_FF2.7, U_FSYNC_FF2.8, U_FSYNC_OR.5, U_TDM_XLATE.16, U_XU.61, Y_AUDIO.1, Y_AUDIO.4
N3V3_ADC: C_ADC_3V3X_OK_VDD.1, C_ADC_A_AVDD_10U.1, C_ADC_A_AVDD_100N.1, C_ADC_A_IOVDD_10U.1, C_ADC_A_IOVDD_100N.1, C_ADC_B_AVDD_10U.1, C_ADC_B_AVDD_100N.1, C_ADC_B_IOVDD_10U.1, C_ADC_B_IOVDD_100N.1, C_ADC_CLOCK_OK.1, C_ADC_DIGITAL_BAD.1, C_ADC_DIGITAL_OK.1, C_ADC_I2C_B.1, C_ADC_OUT.1, C_ADC_READY.1, C_ADC_READY_BAD.1, C_LDO_OUT_1.1, C_LDO_OUT_2.1, C_OPA1.1, C_OPA2.1, C_OPA3.1, C_OPA4.1, C_OPA5.1, C_OPA6.1, C_OPA7.1, C_OPA8.1, C_OPA_BULK.1, C_RST1.1, C_RST2.1, R_ADC_DIGITAL_OK_PU.1, R_ADC_I2C_SCL_B_PU.2, R_ADC_I2C_SDA_B_PU.2, R_ADC_OK_TOP.1, R_ADC_TOP.1, R_DUMP.1, R_LDO_PG_TOP.1, R_OPA_BLEED1.1, R_RESET_PU.1, R_RST_T.1, R_VMID1_TOP.1, R_VMID2_TOP.1, U_ADC_1V8_OK.3, U_ADC_1V8_OK.4, U_ADC_3V3X_OK.3, U_ADC_3V3X_OK.4, U_ADC_A.1, U_ADC_A.19, U_ADC_B.1, U_ADC_B.16, U_ADC_B.19, U_ADC_CLOCK_OK.5, U_ADC_DIGITAL_BAD.5, U_ADC_I2C_XLATE.7, U_ADC_OUT.8, U_ADC_READY.5, U_ADC_READY_BAD.5, U_AFE1.8, U_AFE2.8, U_AFE3.8, U_AFE4.8, U_AFE5.8, U_AFE6.8, U_AFE7.8, U_AFE8.8, U_LDO.9, U_LDO.10, U_RST1.3, U_RST2.8
N5V_BUCK: C_1V8_OK_VDD.1, C_OUT1.1, C_OUT2.1, C_OUT3.1, C_U_1V8_IN_1.1, C_U_1V8_IN_2.1, C_U_3V3X_IN_1.1, C_U_3V3X_IN_2.1, C_U_CORE_IN_1.1, C_U_CORE_IN_2.1, C_VLDO.1, C_XU_3V3_OK_VDD.1, D_HOLD.2, R_BUCK_FB_TOP.1, R_PWR_TOP.1, U_1V8.1, U_1V8.7, U_1V8_OK.3, U_1V8_OK.4, U_3V3X.1, U_3V3X.7, U_BUCK.7, U_BUCK.8, U_BUCK.9, U_BUCK.10, U_BUCK.12, U_BUCK.13, U_BUCK.14, U_BUCK.15, U_BUCK.22, U_BUCK.30, U_CORE.7, U_XU_3V3_OK.3, U_XU_3V3_OK.4
N5V_LDO_FEED: D_HOLD.1, Q_PRE.2, R_PRE.1, R_PRE_G.2
N5V_LDO_HOLD: C_ADC_PWR_BAD.1, C_AUDIO.1, C_DUMP_LOGIC.1, C_HOLD1.1, C_HOLD2.1, C_HOLD3.1, C_HOLD4.1, C_HOLD5.1, C_HOLD6.1, C_HOLD7.1, C_HOLD8.1, C_HOLD9.1, C_HOLD10.1, C_HOLD11.1, C_HOLD12.1, C_HOLD13.1, C_HOLD14.1, C_HOLD15.1, C_HOLD16.1, C_ISO1.1, C_ISO2.1, C_ISO3.1, C_ISO4.1, C_ISO5.1, C_ISO6.1, C_ISO7.1, C_ISO8.1, C_LDO_EN.1, C_LDO_IN.1, C_PWR.1, Q_PRE.3, R_AUDIO_PU.1, R_PRE.2, R_PWR_PU.1, U_ADC_PWR_BAD.5, U_AUDIO.4, U_DUMP.5, U_ISO1.8, U_ISO2.8, U_ISO3.8, U_ISO4.8, U_ISO5.8, U_ISO6.8, U_ISO7.8, U_ISO8.8, U_LDO.1, U_LDO.2, U_LDO_EN.5, U_PWR.3, U_PWR.4
N12V_FUSED: F_IN.2, Q_IN.5
N12V_IN: F_IN.1, J_PWR.1
N12V_POD1: C_SPOKE_OUT1.1, J1.1, J1.3, J1.7, U_SPOKE1.10
N12V_POD2: C_SPOKE_OUT2.1, J2.1, J2.3, J2.7, U_SPOKE2.10
N12V_POD3: C_SPOKE_OUT3.1, J3.1, J3.3, J3.7, U_SPOKE3.10
N12V_POD4: C_SPOKE_OUT4.1, J4.1, J4.3, J4.7, U_SPOKE4.10
N12V_POD5: C_SPOKE_OUT5.1, J5.1, J5.3, J5.7, U_SPOKE5.10
N12V_POD6: C_SPOKE_OUT6.1, J6.1, J6.3, J6.7, U_SPOKE6.10
N12V_POD7: C_SPOKE_OUT7.1, J7.1, J7.3, J7.7, U_SPOKE7.10
N12V_POD8: C_SPOKE_OUT8.1, J8.1, J8.3, J8.7, U_SPOKE8.10
N12V_PROTECTED: C_IN1.1, C_IN2.1, C_IN3.1, C_IN_HF.1, C_SPOKE_IN1.1, C_SPOKE_IN2.1, C_SPOKE_IN3.1, C_SPOKE_IN4.1, C_SPOKE_IN5.1, C_SPOKE_IN6.1, C_SPOKE_IN7.1, C_SPOKE_IN8.1, D_IN.1, D_QIN_GS.1, Q_IN.1, Q_IN.2, Q_IN.3, R_SPOKE_UVLO1.1, R_SPOKE_UVLO2.1, R_SPOKE_UVLO3.1, R_SPOKE_UVLO4.1, R_SPOKE_UVLO5.1, R_SPOKE_UVLO6.1, R_SPOKE_UVLO7.1, R_SPOKE_UVLO8.1, U_BUCK.2, U_BUCK.3, U_BUCK.4, U_BUCK.18, U_BUCK.19, U_SPOKE1.1, U_SPOKE1.4, U_SPOKE2.1, U_SPOKE2.4, U_SPOKE3.1, U_SPOKE3.4, U_SPOKE4.1, U_SPOKE4.4, U_SPOKE5.1, U_SPOKE5.4, U_SPOKE6.1, U_SPOKE6.4, U_SPOKE7.1, U_SPOKE7.4, U_SPOKE8.1, U_SPOKE8.4
OPA_BLEED_A: R_OPA_BLEED1.2, R_OPA_BLEED2.1
OPA_N1: C_FB1N.2, R_OUT1N.1, U_AFE1.7
OPA_N2: C_FB2N.2, R_OUT2N.1, U_AFE2.7
OPA_N3: C_FB3N.2, R_OUT3N.1, U_AFE3.7
OPA_N4: C_FB4N.2, R_OUT4N.1, U_AFE4.7
OPA_N5: C_FB5N.2, R_OUT5N.1, U_AFE5.7
OPA_N6: C_FB6N.2, R_OUT6N.1, U_AFE6.7
OPA_N7: C_FB7N.2, R_OUT7N.1, U_AFE7.7
OPA_N8: C_FB8N.2, R_OUT8N.1, U_AFE8.7
OPA_P1: C_FB1P.2, R_OUT1P.1, U_AFE1.1
OPA_P2: C_FB2P.2, R_OUT2P.1, U_AFE2.1
OPA_P3: C_FB3P.2, R_OUT3P.1, U_AFE3.1
OPA_P4: C_FB4P.2, R_OUT4P.1, U_AFE4.1
OPA_P5: C_FB5P.2, R_OUT5P.1, U_AFE5.1
OPA_P6: C_FB6P.2, R_OUT6P.1, U_AFE6.1
OPA_P7: C_FB7P.2, R_OUT7P.1, U_AFE7.1
OPA_P8: C_FB8P.2, R_OUT8P.1, U_AFE8.1
PLL_0V9: C_PLL_1U.1, C_PLL_100N.1, FB_PLL.2, U_XU.41
POR_N: U_ADC_READY.2, U_RST1.2
PRE_GATE: Q_PRE.1, Q_PRE_EN.3, R_PRE_G.1
PWR_CT: C_PWR_CT.1, C_PWR_CT2.1, C_PWR_CT3.1, U_PWR.5
PWR_EN: Q_PRE_EN.1, R_DUMP_TIME1.1, R_PWR_PU.2, U_ADC_PWR_BAD.2, U_AUDIO.3, U_PWR.6
PWR_SENSE: R_PWR_BOT.1, R_PWR_TOP.2, U_PWR.1
QSPI_CLK: U_FLASH.6, U_XU.4
QSPI_CS_N: R_QSPI_CS.2, U_FLASH.1, U_XU.2
QSPI_D0: U_FLASH.5, U_XU.127
QSPI_D1: U_FLASH.2, U_XU.128
QSPI_D2: U_FLASH.3, U_XU.1
QSPI_D3: U_FLASH.7, U_XU.3
Q_IN_GATE: D_QIN_GS.2, Q_IN.4, R_QIN_G.1
RESET_C: C_RST_T.1, U_RST2.6
RESET_PULSE_H: Q_RST1.1, R_RESET_GPD.1, U_RST2.5
RESET_RC: C_RST_T.2, R_RST_T.2, U_RST2.7
SPOKE_DVDT1: C_SPOKE_DVDT1.1, U_SPOKE1.8
SPOKE_DVDT2: C_SPOKE_DVDT2.1, U_SPOKE2.8
SPOKE_DVDT3: C_SPOKE_DVDT3.1, U_SPOKE3.8
SPOKE_DVDT4: C_SPOKE_DVDT4.1, U_SPOKE4.8
SPOKE_DVDT5: C_SPOKE_DVDT5.1, U_SPOKE5.8
SPOKE_DVDT6: C_SPOKE_DVDT6.1, U_SPOKE6.8
SPOKE_DVDT7: C_SPOKE_DVDT7.1, U_SPOKE7.8
SPOKE_DVDT8: C_SPOKE_DVDT8.1, U_SPOKE8.8
SPOKE_ILIM1: R_SPOKE_ILIM1.1, U_SPOKE1.7
SPOKE_ILIM2: R_SPOKE_ILIM2.1, U_SPOKE2.7
SPOKE_ILIM3: R_SPOKE_ILIM3.1, U_SPOKE3.7
SPOKE_ILIM4: R_SPOKE_ILIM4.1, U_SPOKE4.7
SPOKE_ILIM5: R_SPOKE_ILIM5.1, U_SPOKE5.7
SPOKE_ILIM6: R_SPOKE_ILIM6.1, U_SPOKE6.7
SPOKE_ILIM7: R_SPOKE_ILIM7.1, U_SPOKE7.7
SPOKE_ILIM8: R_SPOKE_ILIM8.1, U_SPOKE8.7
SPOKE_RTN1: C_SPOKE_DVDT1.2, R_SPOKE_ILIM1.2, U_SPOKE1.3, U_SPOKE1.5, U_SPOKE1.11
SPOKE_RTN2: C_SPOKE_DVDT2.2, R_SPOKE_ILIM2.2, U_SPOKE2.3, U_SPOKE2.5, U_SPOKE2.11
SPOKE_RTN3: C_SPOKE_DVDT3.2, R_SPOKE_ILIM3.2, U_SPOKE3.3, U_SPOKE3.5, U_SPOKE3.11
SPOKE_RTN4: C_SPOKE_DVDT4.2, R_SPOKE_ILIM4.2, U_SPOKE4.3, U_SPOKE4.5, U_SPOKE4.11
SPOKE_RTN5: C_SPOKE_DVDT5.2, R_SPOKE_ILIM5.2, U_SPOKE5.3, U_SPOKE5.5, U_SPOKE5.11
SPOKE_RTN6: C_SPOKE_DVDT6.2, R_SPOKE_ILIM6.2, U_SPOKE6.3, U_SPOKE6.5, U_SPOKE6.11
SPOKE_RTN7: C_SPOKE_DVDT7.2, R_SPOKE_ILIM7.2, U_SPOKE7.3, U_SPOKE7.5, U_SPOKE7.11
SPOKE_RTN8: C_SPOKE_DVDT8.2, R_SPOKE_ILIM8.2, U_SPOKE8.3, U_SPOKE8.5, U_SPOKE8.11
SPOKE_UVLO1: R_SPOKE_UVLO1.2, U_SPOKE1.2
SPOKE_UVLO2: R_SPOKE_UVLO2.2, U_SPOKE2.2
SPOKE_UVLO3: R_SPOKE_UVLO3.2, U_SPOKE3.2
SPOKE_UVLO4: R_SPOKE_UVLO4.2, U_SPOKE4.2
SPOKE_UVLO5: R_SPOKE_UVLO5.2, U_SPOKE5.2
SPOKE_UVLO6: R_SPOKE_UVLO6.2, U_SPOKE6.2
SPOKE_UVLO7: R_SPOKE_UVLO7.2, U_SPOKE7.2
SPOKE_UVLO8: R_SPOKE_UVLO8.2, U_SPOKE8.2
TDM_BCLK_1V8: U_TDM_XLATE.4, U_XU.22
TDM_DATA_1V8: U_TDM_XLATE.7, U_XU.107
TDM_FSYNC_1V8: U_TDM_XLATE.5, U_XU.20
TDM_OE_N: Q_TDM_GATE.3, R_TDM_OE_PU.2, U_TDM_XLATE.15
USB_CC1: J_USB.A5, R_USB_CC1.1, U_USB_CC_ESD.3
USB_CC2: J_USB.B5, R_USB_CC2.1, U_USB_CC_ESD.5
USB_DN: J_USB.A7, J_USB.B7, U_USB_ESD.2, U_XU.59
USB_DP: J_USB.A6, J_USB.B6, U_USB_ESD.1, U_XU.60
U_1V8_FB: C_1V8_FF.2, R_1V8_FB_BOTTOM.1, R_1V8_FB_TOP.2, U_1V8.2
U_1V8_OK_SENSE: R_1V8_OK_BOT.1, R_1V8_OK_TOP.2, U_1V8_OK.1
U_1V8_SW: L_U_1V8.1, U_1V8.6
U_3V3X_FB: C_3V3X_FF.2, R_3V3X_FB_BOTTOM.1, R_3V3X_FB_TOP.2, U_3V3X.2
U_3V3X_SW: L_U_3V3X.1, U_3V3X.6
U_ADC_1V8_OK_SENSE: R_ADC_1V8_OK_BOT.1, R_ADC_1V8_OK_TOP.2, U_ADC_1V8_OK.1
U_ADC_3V3X_OK_SENSE: R_ADC_3V3X_OK_BOT.1, R_ADC_3V3X_OK_TOP.2, U_ADC_3V3X_OK.1
U_ADC_OK_SENSE: R_ADC_OK_BOT.1, R_ADC_OK_TOP.2, U_ADC_OK.1
U_CORE_FB: C_CORE_FF.2, R_CORE_FB_BOTTOM.1, R_CORE_FB_TOP.2, U_CORE.2
U_CORE_SW: L_U_CORE.1, U_CORE.6
U_XU_3V3_OK_SENSE: R_XU_3V3_OK_BOT.1, R_XU_3V3_OK_TOP.2, U_XU_3V3_OK.1
VBUS_B: Q_VBUS.1, R_VBUS_B.2, R_VBUS_BE.1
VBUS_PRESENT_N: Q_VBUS.3, R_VBUS_PU.2, U_XU.8
VBUS_USB: C_USB_VBUS.1, J_USB.A4, J_USB.A9, J_USB.B4, J_USB.B9, R_USB_VBUS_BLEED.1, R_VBUS_B.1, U_USB_VBUS_ESD.3
VMID1_EXT: C_VMID1_EXT_1U.1, C_VMID1_EXT_10U.1, R_B1N.2, R_B1P.2, R_B2N.2, R_B2P.2, R_B3N.2, R_B3P.2, R_B4N.2, R_B4P.2, R_VMID1_BOT.1, R_VMID1_TOP.2
VMID2_EXT: C_VMID2_EXT_1U.1, C_VMID2_EXT_10U.1, R_B5N.2, R_B5P.2, R_B6N.2, R_B6P.2, R_B7N.2, R_B7P.2, R_B8N.2, R_B8P.2, R_VMID2_BOT.1, R_VMID2_TOP.2
XTAL_IN: R_XTAL_DRIVE.1, R_XTAL_FB.1, U_XU.34
XTAL_IN_R: C_XTAL_IN.1, R_XTAL_DRIVE.2, Y_XU.1
XTAL_OUT: C_XTAL_OUT.1, R_XTAL_FB.2, U_XU.33, Y_XU.3
XU_3V3_OK_CT: C_XU_3V3_OK_CT.1, U_XU_3V3_OK.5
XU_I2C_SCL_1V8: R_ADC_I2C_SCL_A_PU.1, U_ADC_I2C_XLATE.5, U_XU.93
XU_I2C_SDA_1V8: R_ADC_I2C_SDA_A_PU.1, U_ADC_I2C_XLATE.4, U_XU.94
XU_RESET_N: J_JTAG.10, R_XU_RST_PU.2, U_CORE_OK.1, U_XU.38, U_XU_3V3_OK.6
